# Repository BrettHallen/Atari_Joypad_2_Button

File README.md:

# Atari Joypad (Two Button) aka Brett's Clueless Joypad
Simple two-button joypad using Atari pinout, compatible with both Atari 2600 & Atari 7800.<br>

Its purpose is for use as a small "troubleshooting" joypad when you are trying to repair a vintage computer and you have its bare motherboard on the bench.<br>

It has no higher aspirations than that.<br>

It is no larger than 100mm so its fabrication falls under the cheapest PCB cost (i.e. ten PCBs for US$5 at PCBWAY).<br>

There are three [right handed](/RightHanded) versions:<br>
- Rev. A matches the Atari 7800 layout: FIRE1 on left, FIRE2 on right
- Rev. B matches the NES layout: FIRE1/A on right, FIRE2/B on left
- Rev. C where FIRE1/FIRE2 position is selectable via solder bridge (default is Rev. A layout)

In testing I found my right thumb naturally resting on the FIRE2 (rightmost) button, hence the Rev. B design.  The Rev. C design has them selectable via solder bridge (thanks to suggestion by SheldonHarold/YouTube).<br>

Of course using it with something that expects Atari 2600 it doesn't matter as both FIRE buttons function the same.<br>

I have started a [left-handed](/LeftHanded) version ... any need?

## YouTube Videos
- [Part 1: Initial test (right handed, Rev. A)](https://youtu.be/WF11pfEDQUY)

## [Paddle](/Paddle)
Design for a troubleshooting paddle based on Atari design (thanks to suggestion by Ascania/YouTube).<br>

Suggested linear potentiometer values I've seen are 1MΩ for Atari and 470KΩ for Commodore.<br>

## [MSX Adaptor](/MSX_Adaptor)
I had an idea that an MSX adaptor board could be connected underneath the Atari 2600/7800 board.<br>

The one joypad could then be connected natively to either Atari 2600/7800 (top PCB) or MSX (bottom PCB).<br>

??<br>

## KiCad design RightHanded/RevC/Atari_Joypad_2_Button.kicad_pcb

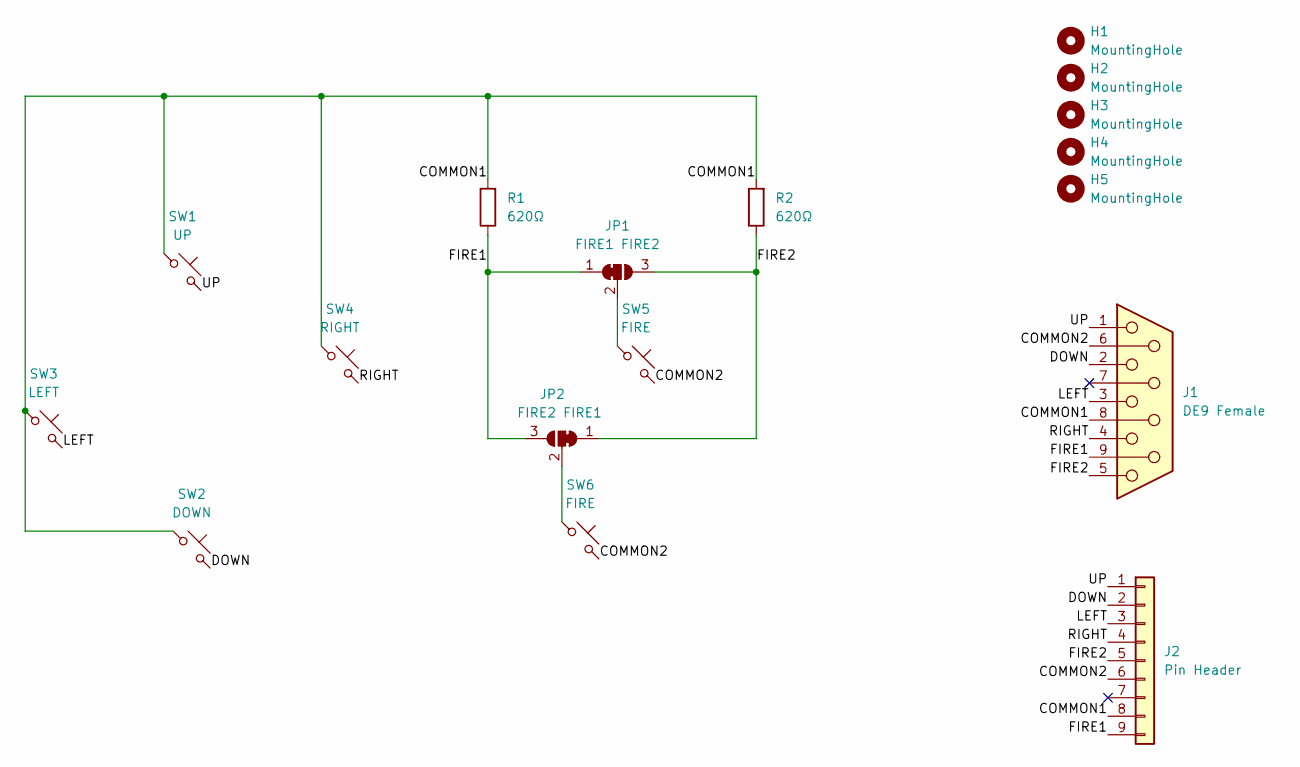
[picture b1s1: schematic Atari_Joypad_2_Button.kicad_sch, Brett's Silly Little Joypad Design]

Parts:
H1, H2, H3, H4, H5: MountingHole; MountingHole_3.2mm_M3_DIN965
J1: DE9 Female; DSUB-9_Socket_EdgeMount_P2.77mm
J2: Pin Header; PinHeader_1x09_P2.54mm_Vertical
JP1: FIRE1 FIRE2; SolderJumper-3_P1.3mm_Bridged12_RoundedPad1.0x1.5mm
JP2: FIRE2 FIRE1; SolderJumper-3_P1.3mm_Bridged12_RoundedPad1.0x1.5mm
R1, R2: 620Ω; R_Axial_DIN0207_L6.3mm_D2.5mm_P7.62mm_Horizontal
SW1: UP; SW_PUSH-12mm
SW2: DOWN; SW_PUSH-12mm
SW3: LEFT; SW_PUSH-12mm
SW4: RIGHT; SW_PUSH-12mm
SW5, SW6: FIRE; SW_PUSH-12mm

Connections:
/COMMON1: J1.8, J2.8, R1.2, R2.2, SW1.1, SW2.1, SW3.1, SW4.1
/COMMON2: J1.6, J2.6, SW5.2, SW6.2
/DOWN: J1.2, J2.2, SW2.2
/FIRE1: J1.9, J2.9, JP1.1 (A), JP2.3 (B), R1.1
/FIRE2: J1.5, J2.5, JP1.3 (B), JP2.1 (A), R2.1
/LEFT: J1.3, J2.3, SW3.2
/RIGHT: J1.4, J2.4, SW4.2
/UP: J1.1, J2.1, SW1.2
unnamed: JP1.2 (C), SW5.1
unnamed: JP2.2 (C), SW6.1

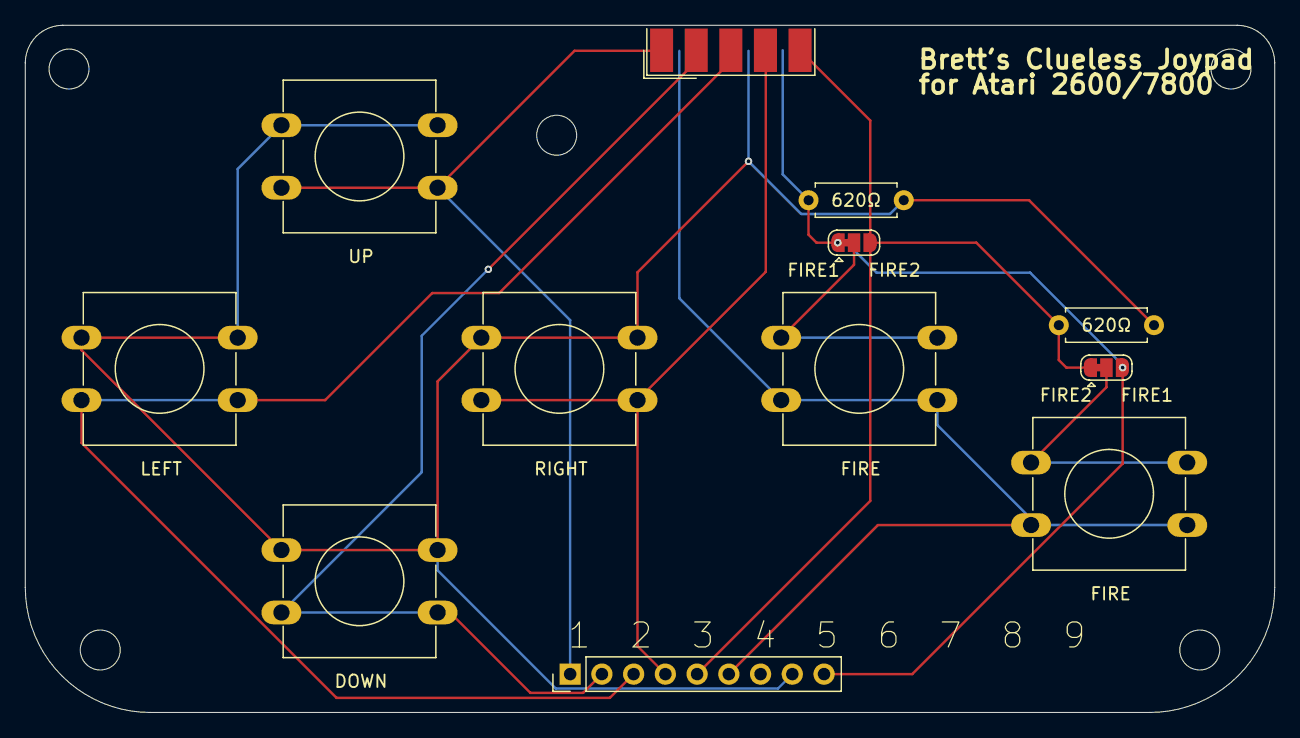
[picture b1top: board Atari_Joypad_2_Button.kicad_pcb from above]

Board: 2 copper layers, 100.0 x 55.0 mm, 17 parts (0 on the bottom side), 10 nets.

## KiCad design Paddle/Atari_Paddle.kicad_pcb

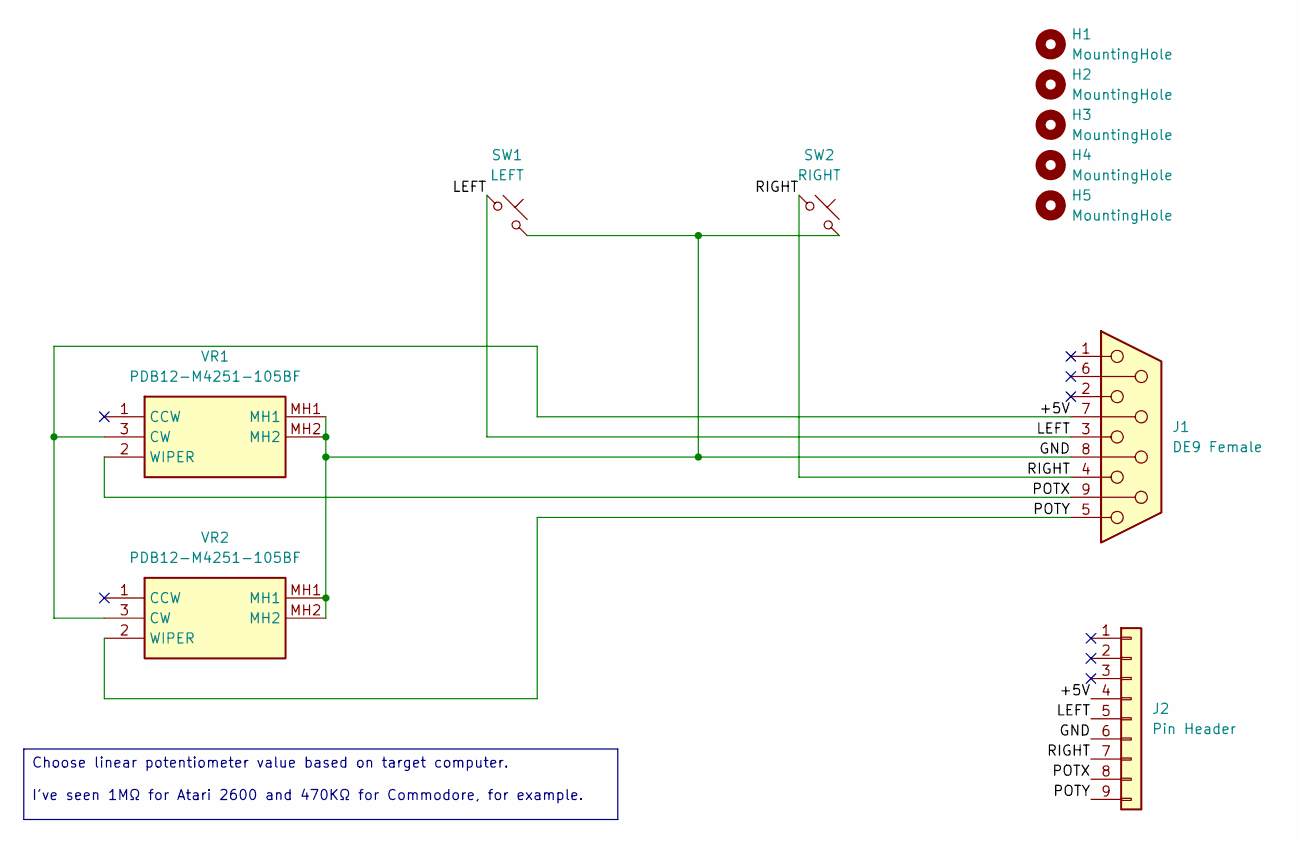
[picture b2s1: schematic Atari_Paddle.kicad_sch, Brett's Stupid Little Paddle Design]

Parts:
H1, H2, H3, H4, H5: MountingHole; MountingHole_3.2mm_M3_DIN965
J1: DE9 Female; DSUB-9_Socket_EdgeMount_P2.77mm
J2: Pin Header; PinHeader_1x09_P2.54mm_Vertical
SW1: LEFT; SW_PUSH-12mm
SW2: RIGHT; SW_PUSH-12mm
VR1, VR2: PDB12-M4251-105BF; PDB12M4251105BF; Mouser Part Number 652-PDB12-M4251105BF

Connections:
/+5V: J1.7, J2.4, VR1.3 (CW), VR2.3 (CW)
/GND: J1.8, J2.6, SW1.2, SW2.2, VR1.MH1, VR1.MH2, VR2.MH1, VR2.MH2
/LEFT: J1.3, J2.5, SW1.1
/POTX: J1.9, J2.8, VR1.2 (WIPER)
/POTY: J1.5, J2.9, VR2.2 (WIPER)
/RIGHT: J1.4, J2.7, SW2.1

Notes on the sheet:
Choose linear potentiometer value based on target computer. I've seen 1MΩ for Atari 2600 and 470KΩ for Commodore, for example.

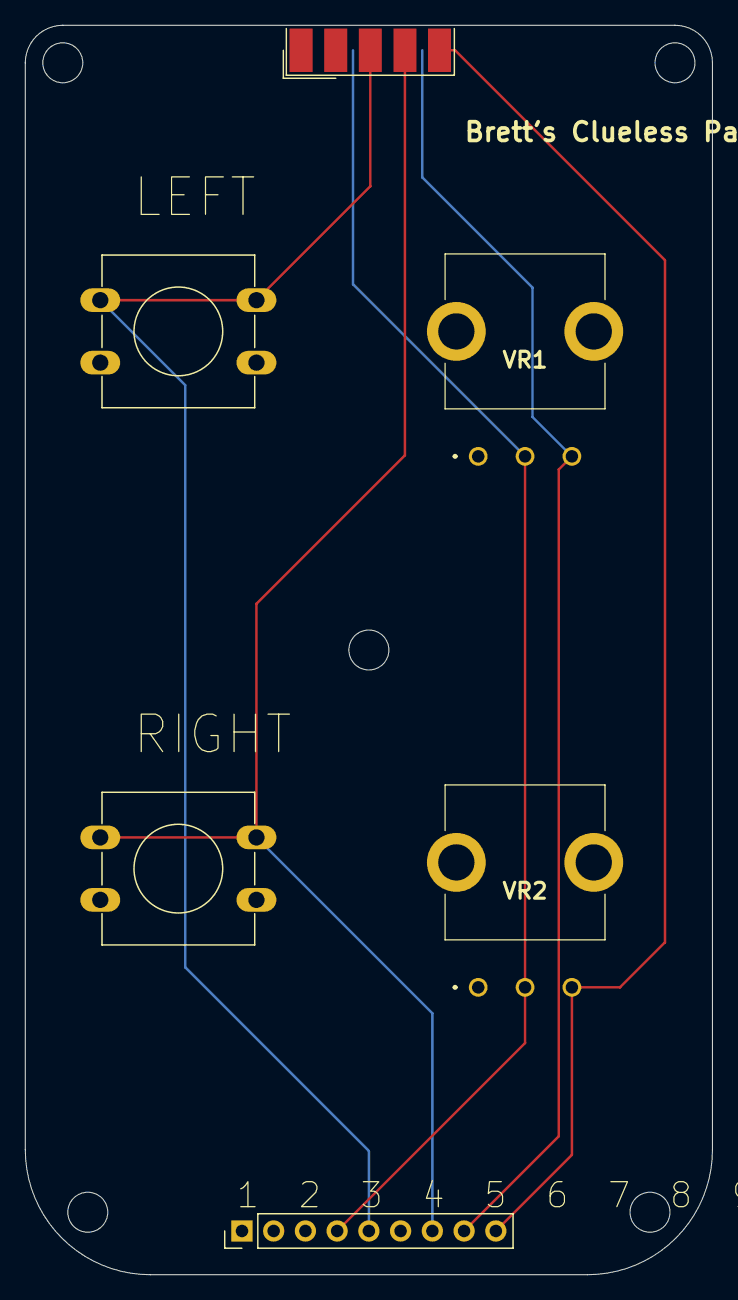
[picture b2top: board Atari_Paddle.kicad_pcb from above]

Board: 2 copper layers, 55.0 x 100.0 mm, 11 parts (0 on the bottom side), 6 nets.

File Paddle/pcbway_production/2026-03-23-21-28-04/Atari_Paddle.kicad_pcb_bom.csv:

Designator,Quantity,Value,Footprint,Package,MPN,DNP,Mount_Type,Description,Height,Mouser Part Number,Mouser Price/Stock,Manufacturer_Name
J1,1,DE9 Female,DSUB-9_Socket_EdgeMount_P2.77mm,,,,smt,"9-pin D-SUB connector, socket (female)",,,,
J2,1,Pin Header,PinHeader_1x09_P2.54mm_Vertical,,,,tht,"Generic connector, single row, 01x09, script generated (kicad-library-utils/schlib/autogen/connector/)",,,,
SW1,1,LEFT,SW_PUSH-12mm,,,,tht,"Push button switch, normally open, two pins, 45° tilted",,,,
SW2,1,RIGHT,SW_PUSH-12mm,,,,tht,"Push button switch, normally open, two pins, 45° tilted",,,,
"VR1, VR2",2,PDB12-M4251-105BF,PDB12M4251105BF,,PDB12-M4251-105BF,,tht,Potentiometers 1M LINEAR 12MM,25,652-PDB12-M4251105BF,https://www.mouser.co.uk/ProductDetail/Bourns/PDB12-M4251-10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,Bourns

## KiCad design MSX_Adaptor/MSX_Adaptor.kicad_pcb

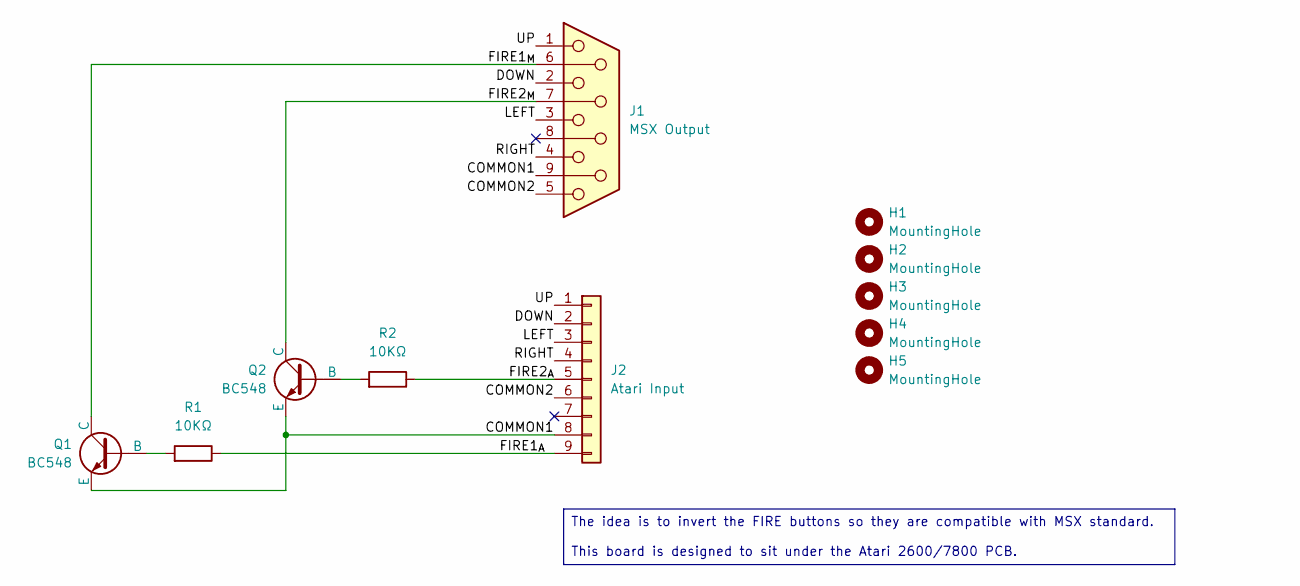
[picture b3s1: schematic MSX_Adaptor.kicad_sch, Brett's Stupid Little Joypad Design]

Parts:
H1, H2, H3, H4, H5: MountingHole; MountingHole_3.2mm_M3_DIN965
J1: MSX Output; DSUB-9_Socket_EdgeMount_P2.77mm
J2: Atari Input; PinHeader_1x09_P2.54mm_Vertical
Q1, Q2: BC548; TO-92_Inline
R1, R2: 10KΩ; R_Axial_DIN0207_L6.3mm_D2.5mm_P7.62mm_Horizontal

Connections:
/COMMON1: J1.9, J2.8, Q1.3 (E), Q2.3 (E)
/COMMON2: J1.5, J2.6
/DOWN: J1.2, J2.2
/FIRE1_{A}: J2.9, R1.1
/FIRE1_{M}: J1.6, Q1.1 (C)
/FIRE2_{A}: J2.5, R2.1
/FIRE2_{M}: J1.7, Q2.1 (C)
/LEFT: J1.3, J2.3
/RIGHT: J1.4, J2.4
/UP: J1.1, J2.1
unnamed: Q1.2 (B), R1.2
unnamed: Q2.2 (B), R2.2

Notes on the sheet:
The idea is to invert the FIRE buttons so they are compatible with MSX standard. This board is designed to sit under the Atari 2600/7800 PCB.

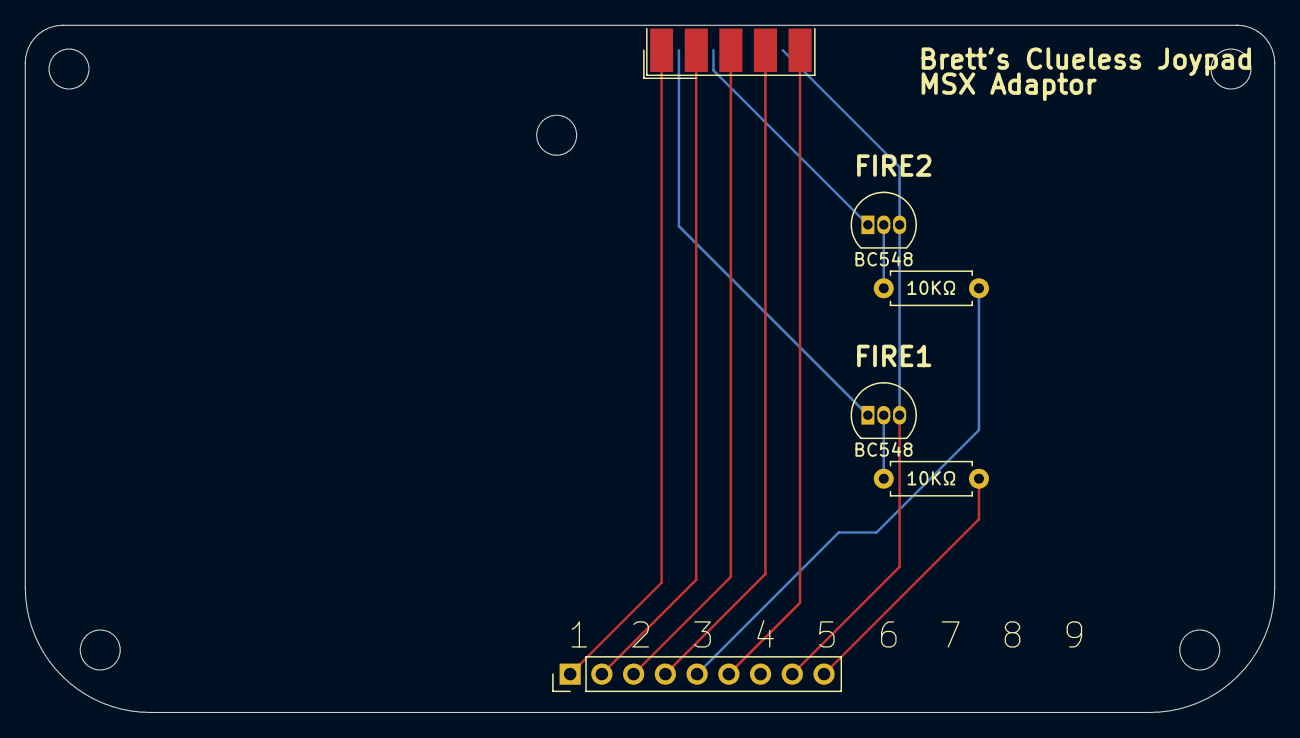
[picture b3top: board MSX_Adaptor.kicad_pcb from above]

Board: 2 copper layers, 100.0 x 55.0 mm, 11 parts (0 on the bottom side), 12 nets.

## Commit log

2026-03-23 Moved to Rev. A folder
2026-03-23 Swapped FIRE1 & FIRE2 positions (matches NES Joypad)
2026-03-23 Initial left-handed design
2026-03-23 Idea for an MSX adaptor
2026-03-23 Possible paddle design
2026-03-23 Add RevA naming
2026-03-23 Add RevB naming
2026-03-23 Added Rev C with selectable FIRE1/FIRE2 position
2026-03-23 Atari-like font used on PCBs
